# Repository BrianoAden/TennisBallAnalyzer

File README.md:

# Introduction
Hi! My name is Aden Briano, and I've created this repository to store all of the code developed for a Tennis Ball Analyzer project I'm working on.
# General Overview
The goal of this project is to create a handheld device capable of testing the suitability of tennis balls for competitive play. 
# Code Overview
Insert Text Here

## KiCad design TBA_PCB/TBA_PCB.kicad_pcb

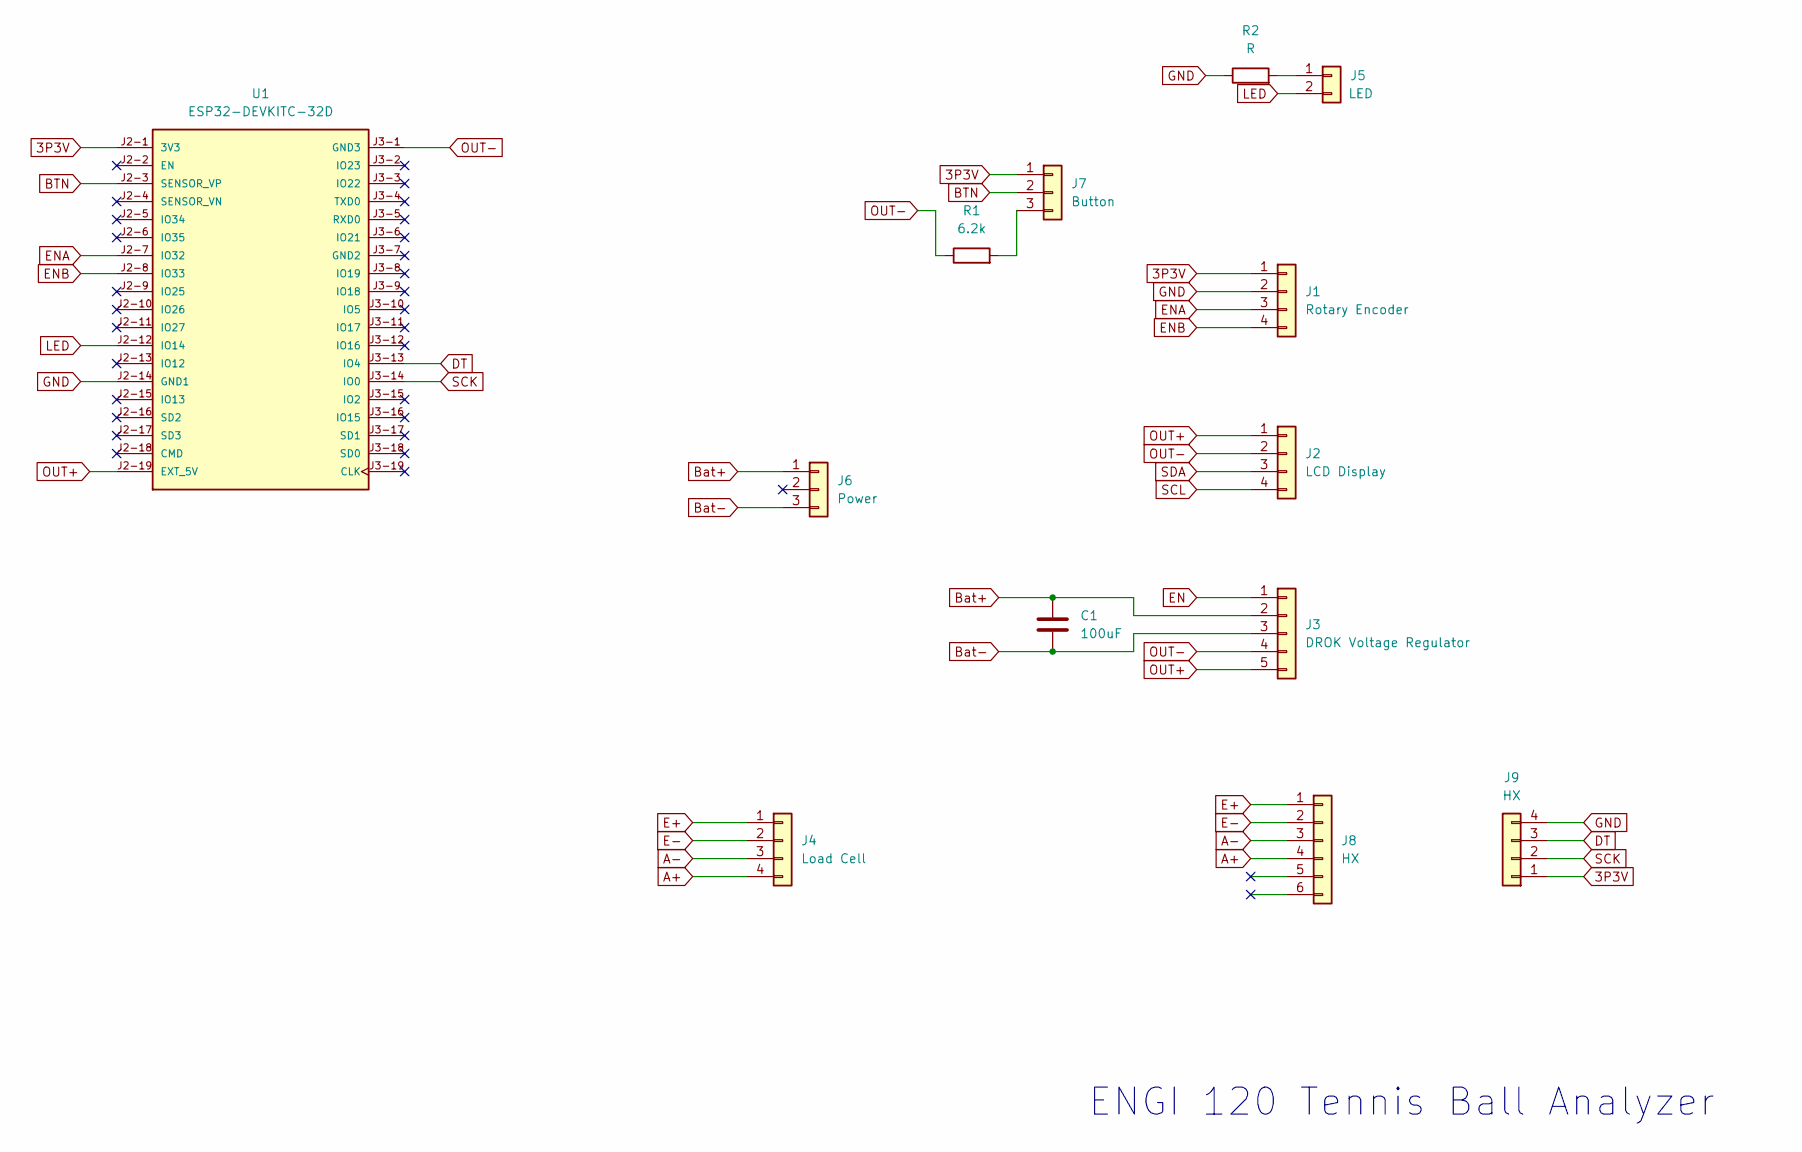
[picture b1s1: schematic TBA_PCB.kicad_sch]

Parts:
C1: 100uF; CP_Radial_D4.0mm_P2.00mm
J1: Rotary Encoder; PinHeader_1x04_P2.54mm_Vertical
J2: LCD Display; PinHeader_1x04_P2.54mm_Vertical
J3: DROK Voltage Regulator; PinHeader_1x05_P2.54mm_Vertical
J4: Load Cell; PinHeader_1x04_P2.54mm_Vertical
J5: LED; PinHeader_1x02_P2.54mm_Vertical
J6: Power; PinHeader_1x03_P2.54mm_Vertical
J7: Button; PinHeader_1x03_P2.54mm_Vertical
J8: HX; PinHeader_1x06_P2.54mm_Vertical
J9: HX; PinHeader_1x04_P2.54mm_Vertical
R1: 6.2k; R_Axial_DIN0204_L3.6mm_D1.6mm_P2.54mm_Vertical
R2: R; R_Axial_DIN0204_L3.6mm_D1.6mm_P2.54mm_Vertical
U1: ESP32-DEVKITC-32D; MODULE_ESP32-DEVKITC-32D; PARTREV V4

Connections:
3P3V: J1.1, J7.1, J9.1, U1.J2-1 (3V3)
A+: J4.4, J8.4
A-: J4.3, J8.3
BTN: J7.2, U1.J2-3 (SENSOR_VP)
Bat+: C1.1, J3.2, J6.1
Bat-: C1.2, J3.3, J6.3
DT: J9.3, U1.J3-13 (IO4)
E+: J4.1, J8.1
E-: J4.2, J8.2
EN: J3.1
ENA: J1.3, U1.J2-7 (IO32)
ENB: J1.4, U1.J2-8 (IO33)
GND: J1.2, J9.4, R2.1, U1.J2-14 (GND1)
LED: J5.2, U1.J2-12 (IO14)
unnamed: J5.1, R2.2
unnamed: J7.3, R1.2
OUT+: J2.1, J3.5, U1.J2-19 (EXT_5V)
OUT-: J2.2, J3.4, R1.1, U1.J3-1 (GND3)
SCK: J9.2, U1.J3-14 (IO0)
SCL: J2.4
SDA: J2.3

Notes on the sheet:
ENGI 120 Tennis Ball Analyzer

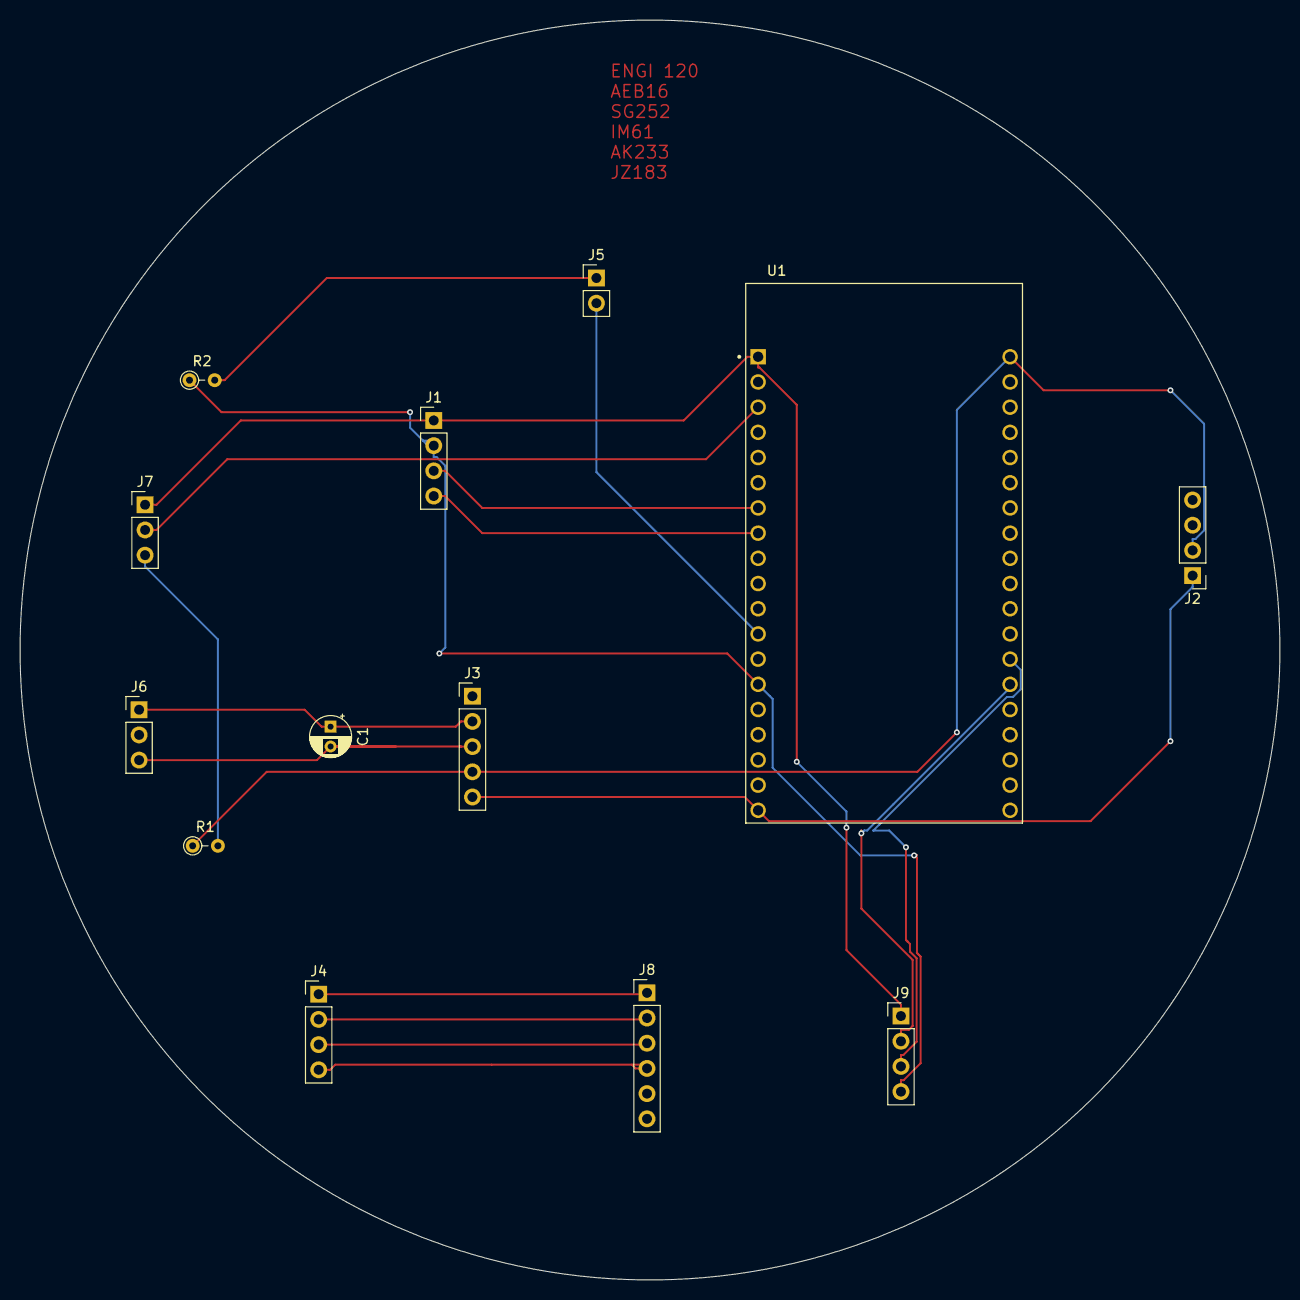
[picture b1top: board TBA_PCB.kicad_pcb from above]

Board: 2 copper layers, 127.0 x 127.0 mm, 13 parts (0 on the bottom side), 18 nets.

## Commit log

2025-04-02 added code developed before the construction of this repository
2025-04-04 fixed rotary encoder code
2025-04-06 made code more modular and included rotary encoder reset
2025-04-14 separated functionalities into esp32 and arduino compatible
2025-04-27 including allcode and files worked on prior to Engineering showcase
2025-04-27 Testing new SSH key
2025-04-27 removed extraneous file
2025-04-30 included practice threshold, updated PCB, gathered new data to plot
